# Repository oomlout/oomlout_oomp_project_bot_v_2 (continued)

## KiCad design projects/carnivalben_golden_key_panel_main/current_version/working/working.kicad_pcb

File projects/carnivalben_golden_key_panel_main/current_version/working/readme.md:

# golden_key
 
## summary 
* id: carnivalben_golden_key_panel_main
* user: carnivalben
* name: golden_key
* board: panel_main
* repo: https://github.com/CarnivalBen/golden-key
* src_file_repo_kicad_pcb: panel/pcb-main/panel-main - Copy.kicad_pcb
* src_file_repo_kicad_pcb_link: https://github.com/CarnivalBen/golden-key/tree/master/panel/pcb-main/panel-main - Copy.kicad_pcb

* src_file_repo_sch: layout-diag/layout-diag.sch
* src_file_repo_sch_link: https://github.com/CarnivalBen/golden-key/tree/master/layout-diag/layout-diag.sch
* full details link: https://github.com/oomlout/oomlout_oomp_project_bot_v_2/tree/main/projects/carnivalben_golden_key_panel_main/current_version/working  

## pcb  

[board (pdf)](working.pdf)  

## working_bom
| Id | Designator | Footprint | Quantity | Designation | Supplier and ref |  | None | 
| --- | --- | --- | --- | --- | --- | --- | --- | 
| 1 | C1,C2 | CP_Radial_D10.0mm_P5.00mm | 2 | 470uF |  |  | [''] | 
| 2 | C3 | C_Disc_D4.7mm_W2.5mm_P5.00mm | 1 | 10nF |  |  | [''] | 
| 3 | C4,C5 | C_Disc_D3.4mm_W2.1mm_P2.50mm | 2 | 33pF |  |  | [''] | 
| 4 | C6,C7 | CP_Radial_D18.0mm_P7.50mm | 2 | 4700uF |  |  | [''] | 
| 5 | D1,D2,D3,D4,D5,D6,D7,D8,D9,D10,D11,D12,D13,D14,D15,D16,D17,D18 | D_DO-15_P12.70mm_Horizontal | 18 | 1N4001 |  |  | [''] | 
| 6 | D19 | D_DO-15_P10.16mm_Horizontal | 1 | 12V |  |  | [''] | 
| 7 | D20 | D_DO-15_P10.16mm_Horizontal | 1 | 5V |  |  | [''] | 
| 8 | J1 | Wire_Pads_Edge_1x2 | 1 | PSU IN |  |  | [''] | 
| 9 | J2 | DIN_Socket_Edge_Solder_4pin | 1 | SPEED CTRL |  |  | [''] | 
| 10 | J3 | Pin_Header_Straight_1x06_Pitch2.54mm | 1 | ICSP |  |  | [''] | 
| 11 | J5 | Pin_Header_Straight_2x06_Pitch2.54mm | 1 | DISPLAY |  |  | [''] | 
| 12 | J6 | Wire_Pads_Edge_2x8 | 1 | CONN-L1 |  |  | [''] | 
| 13 | J7 | Wire_Pads_Edge_2x8 | 1 | CONN-L2 |  |  | [''] | 
| 14 | J8 | Wire_Pads_Edge_2x8 | 1 | CONN-R1 |  |  | [''] | 
| 15 | J9 | Wire_Pads_Edge_2x3 | 1 | CONN-R2 |  |  | [''] | 
| 16 | K1,K2,K3,K4,K5,K6,K7,K8,K9,K10,K11 | TRK22X3-XXDC | 11 | TRK2233-12DC |  |  | [''] | 
| 17 | Q1,Q14 | TO-92_Inline_Wide | 2 | 2N2222 |  |  | [''] | 
| 18 | Q2,Q9 | TO-220-3_Vertical | 2 | TIP32 |  |  | [''] | 
| 19 | Q3,Q4,Q5,Q6,Q7,Q8,Q10,Q11,Q12,Q13,Q15,Q16,Q17,Q18,Q19,Q37 | TO-126_Vertical | 16 | BD679 |  |  | [''] | 
| 20 | R1 | R_Axial_DIN0207_L6.3mm_D2.5mm_P10.16mm_Horizontal | 1 | 10K |  |  | [''] | 
| 21 | R2,R3,R8,R9 | R_Axial_DIN0207_L6.3mm_D2.5mm_P10.16mm_Horizontal | 4 | 5K |  |  | [''] | 
| 22 | R4,R5,R6,R7,R10,R11,R12,R13,R14,R15,R16,R17,R18,R19,R20,R21 | R_Axial_DIN0207_L6.3mm_D2.5mm_P10.16mm_Horizontal | 16 | 1K |  |  | [''] | 
| 23 | U1 | TO-220-3_Vertical | 1 | LM7805_TO220 |  |  | [''] | 
| 24 | U2,U3,U4,U5 | DIP-16_W7.62mm_LongPads | 4 | 74HC595 |  |  | [''] | 
| 25 | U6,U7 | DIP-16_W7.62mm_LongPads | 2 | ULN2003A |  |  | [''] | 
| 26 | U***1 | DIP-40_W15.24mm_LongPads | 1 | PIC16F877A |  |  | [''] | 
| 27 | Y1 | Crystal_HC49-U_Vertical | 1 | 20MHz |  |  | [''] | 
| 28 | J4 | Pin_Header_Straight_2x06_Pitch2.54mm | 1 | PUSH-BUTTON |  |  | [''] |

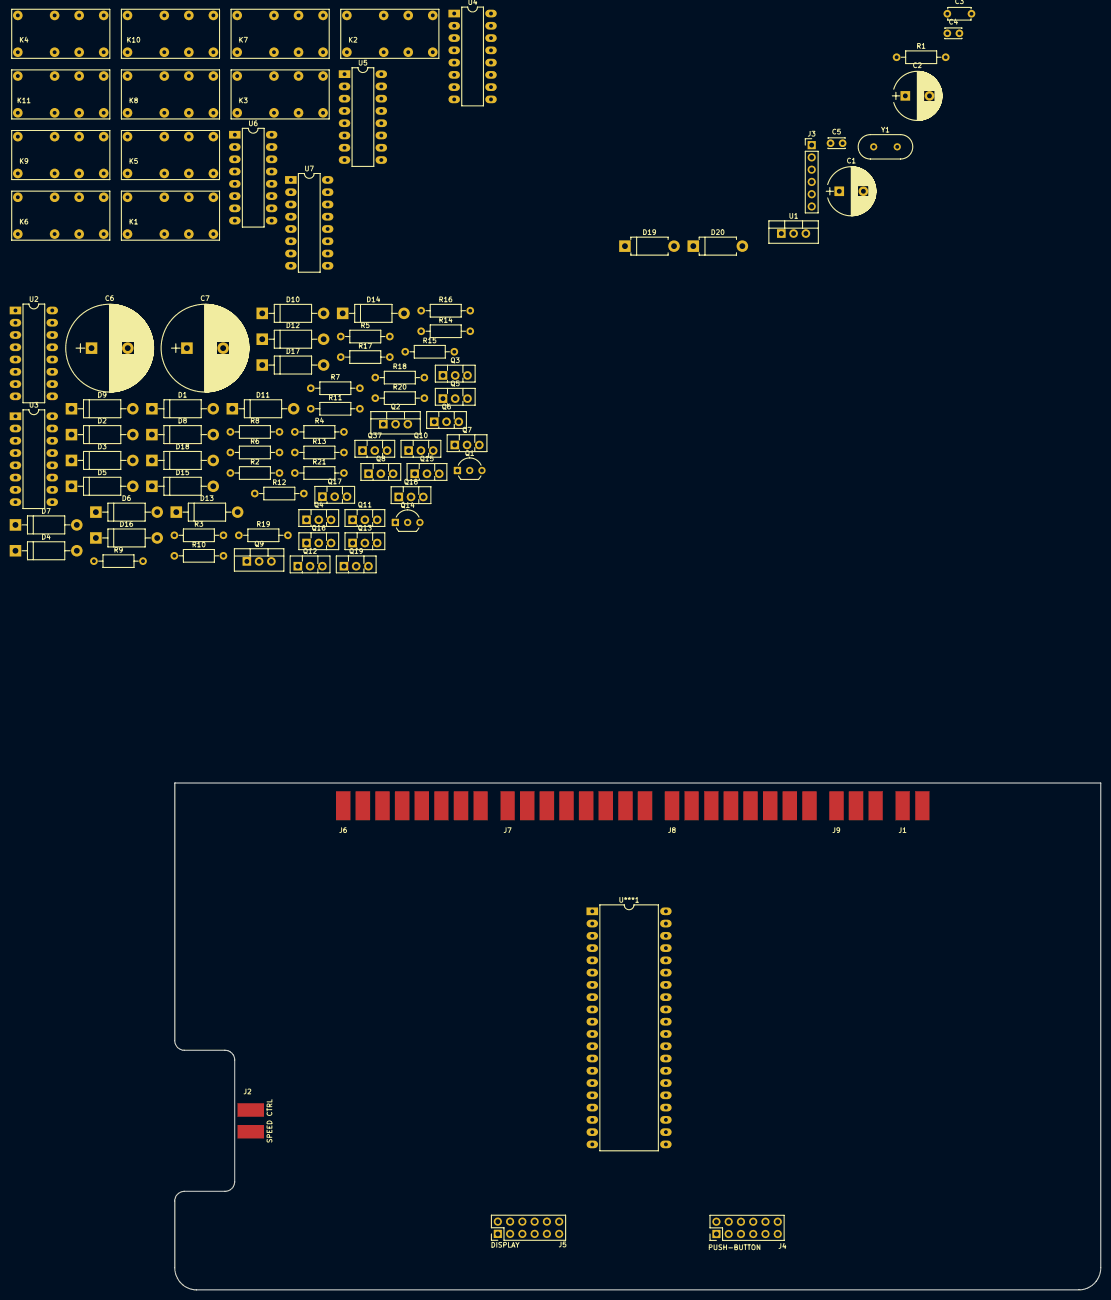
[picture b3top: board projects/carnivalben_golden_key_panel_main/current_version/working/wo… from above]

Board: 2 copper layers, 191.7 x 104.9 mm, 97 parts (0 on the bottom side), 131 nets, no tracks yet.

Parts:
C1, C2: 470uF; CP_Radial_D10.0mm_P5.00mm
C3: 10nF; C_Disc_D4.7mm_W2.5mm_P5.00mm
C4, C5: 33pF; C_Disc_D3.4mm_W2.1mm_P2.50mm
C6, C7: 4700uF; CP_Radial_D18.0mm_P7.50mm
D1, D2, D3, D4, D5, D6, D7, D8, D9, D10, D11, D12, D13, D14, D15, D16, D17, D18: 1N4001; D_DO-15_P12.70mm_Horizontal
D19: 12V; D_DO-15_P10.16mm_Horizontal
D20: 5V; D_DO-15_P10.16mm_Horizontal
J1: PSU IN; Wire_Pads_Edge_1x2
J2: SPEED CTRL; DIN_Socket_Edge_Solder_4pin
J3: ICSP; Pin_Header_Straight_1x06_Pitch2.54mm
J4: PUSH-BUTTON; Pin_Header_Straight_2x06_Pitch2.54mm
J5: DISPLAY; Pin_Header_Straight_2x06_Pitch2.54mm
J6: CONN-L1; Wire_Pads_Edge_2x8
J7: CONN-L2; Wire_Pads_Edge_2x8
J8: CONN-R1; Wire_Pads_Edge_2x8
J9: CONN-R2; Wire_Pads_Edge_2x3
K1, K2, K3, K4, K5, K6, K7, K8, K9, K10, K11: TRK2233-12DC; TRK22X3-XXDC
Q1, Q14: 2N2222; TO-92_Inline_Wide
Q2, Q9: TIP32; TO-220-3_Vertical
Q3, Q4, Q5, Q6, Q7, Q8, Q10, Q11, Q12, Q13, Q15, Q16, Q17, Q18, Q19, Q37: BD679; TO-126_Vertical
R1: 10K; R_Axial_DIN0207_L6.3mm_D2.5mm_P10.16mm_Horizontal
R2, R3, R8, R9: 5K; R_Axial_DIN0207_L6.3mm_D2.5mm_P10.16mm_Horizontal
R4, R5, R6, R7, R10, R11, R12, R13, R14, R15, R16, R17, R18, R19, R20, R21: 1K; R_Axial_DIN0207_L6.3mm_D2.5mm_P10.16mm_Horizontal
U1: LM7805_TO220; TO-220-3_Vertical
U2, U3, U4, U5: 74HC595; DIP-16_W7.62mm_LongPads
U6, U7: ULN2003A; DIP-16_W7.62mm_LongPads
U***1: PIC16F877A; DIP-40_W15.24mm_LongPads
Y1: 20MHz; Crystal_HC49-U_Vertical

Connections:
+5V: C2.1, C3.1, D20.1, J3.2, J5.4, J5.12, J7.13, R1.2, U1.3, U2.10, U2.16, U3.10, U3.16, U4.10, U4.16, U5.10, U5.16, U***1.11, U***1.32
+12V: C1.1, D1.2, D4.2, D19.1, J1.2, J2.4, J5.1, K1.1, K2.1, K3.1, K4.1, K5.1, K6.1, K6.3, K6.6, K7.1, K8.1, K9.1, K9.3, K9.6, K10.1, K11.1, U1.1, U6.9, U7.9
/AUX1-LED: J5.11, U***1.25
/AUX2-LED: J5.10, U***1.26
/Feed Relays/AUX[1]: J7.5, J9.1, K6.4, K6.5
/Feed Relays/AUX[2]: J7.6, J9.2, K9.4, K9.5
/Feed Relays/DATA[IN]: U4.14, U***1.15
/Feed Relays/FEED[A+]: J6.1, J8.1, K1.4
/Feed Relays/FEED[A-]: J6.2, K1.5
/Feed Relays/FEED[B+]: J8.2, K3.4
/Feed Relays/FEED[B-]: J8.3, K3.5
/Feed Relays/FEED[C+]: J6.3, J8.4, K5.4
/Feed Relays/FEED[C-]: J6.4, J8.5, K5.5
/Feed Relays/FEED[D+]: J6.5, K7.4
/Feed Relays/FEED[D-]: J6.6, J8.6, K7.5
/Feed Relays/FEED[E+]: J7.1, K8.4, K8.5
/Feed Relays/FEED[F+]: J7.2, K10.4, K10.5
/Feed Relays/FEED[G+]: J7.3, K11.4, K11.5
/Feed Relays/FEED[H+]: J7.4, K2.4, K2.5
/Feed Relays/FEED[I-]: J8.7, K4.4, K4.5
/HALL[E]: J7.12, U***1.4
/HALL[F]: J7.11, U***1.3
/HALL[G]: J7.10, U***1.2
/PB1: J4.1, U***1.30
/PB2: J4.2, U***1.29
/PB3: J4.3, U***1.28
/PB4: J4.4, U***1.27
/PB5: J4.5, U***1.22
/PB6: J4.12, U***1.21
/PB7: J4.11, U***1.20
/PB8: J4.10, U***1.19
/PB9: J4.9, U***1.8
/PB10: J4.8, U***1.9
/Points Control/DATA[IN]: U2.14, U5.9
/Points Control/DATA[OUT]: J5.2, U3.9
/Points Control/PB1: R4.1, U2.15
/Points Control/PB2: R6.1, U2.1
/Points Control/PB3: R10.1, U2.2
/Points Control/PB4: R12.1, U2.3
/Points Control/PB5: R14.1, U2.4
/Points Control/PB6: R16.1, U2.5
/Points Control/PB7: R18.1, U2.6
/Points Control/PB8: R20.1, U2.7
/Points Control/PF1: R5.1, U3.15
/Points Control/PF2: R7.1, U3.1
/Points Control/PF3: R11.1, U3.2
/Points Control/PF4: R13.1, U3.3
/Points Control/PF5: R15.1, U3.4
/Points Control/PF6: R17.1, U3.5
/Points Control/PF7: R19.1, U3.6
/Points Control/PF8: R21.1, U3.7
/Points Control/POINTS[B1]-COIL: D2.1, J8.16, Q37.3
/Points Control/POINTS[B2]-COIL: D5.1, J8.14, Q4.3
/Points Control/POINTS[B3]-COIL: D7.1, J8.12, Q6.3
/Points Control/POINTS[B4]-COIL: D9.1, J8.10, Q8.3
/Points Control/POINTS[B5]-COIL: D11.1, J6.16, Q11.3
/Points Control/POINTS[B6]-COIL: D13.1, J6.14, Q13.3
/Points Control/POINTS[B7]-COIL: D15.1, J6.12, Q16.3
/Points Control/POINTS[B8]-COIL: D17.1, J6.10, Q18.3
/Points Control/POINTS[F1]-COIL: D3.1, J8.15, Q3.3
/Points Control/POINTS[F2]-COIL: D6.1, J8.13, Q5.3
/Points Control/POINTS[F3]-COIL: D8.1, J8.11, Q7.3
/Points Control/POINTS[F4]-COIL: D10.1, J8.9, Q10.3
/Points Control/POINTS[F5]-COIL: D12.1, J6.15, Q12.3
/Points Control/POINTS[F6]-COIL: D14.1, J6.13, Q15.3
/Points Control/POINTS[F7]-COIL: D16.1, J6.11, Q17.3
/Points Control/POINTS[F8]-COIL: D18.1, J6.9, Q19.3
/Points Control/TANK[1]: R2.2, U***1.33
/Points Control/TANK[2]: R9.2, U***1.34
DCLK: J5.3, U2.11, U3.11, U4.11, U5.11, U***1.16
DLAT: J5.5, U2.12, U3.12, U4.12, U5.12, U***1.17
GND: C1.2, C2.2, C3.2, C4.2, C5.2, C6.2, C7.2, D2.2, D3.2, D5.2, D6.2, D7.2, D8.2, D9.2, D10.2, D11.2, D12.2, D13.2, D14.2, D15.2, D16.2, D17.2, D18.2, D19.2, D20.2, J1.1, J2.1, J3.3, J5.8, J6.7, J6.8, J7.7, J7.8, J7.9, J9.4, J9.5, J9.6, Q1.3, Q14.3, U1.2, U2.8, U2.13, U3.8, U3.13, U4.8, U4.13, U5.8, U5.13, U6.8, U7.8, U***1.12, U***1.31
ICSPCLK: J3.5, U***1.39
ICSPDAT: J3.4, U***1.40
MCLR: J3.1, R1.1, U***1.1
unnamed: C4.1, U***1.13, Y1.1
unnamed: C5.1, U***1.14, Y1.2
unnamed: C6.1, D1.1, Q2.3
unnamed: C7.1, D4.1, Q9.3
unnamed: K1.8, U6.16
unnamed: K2.8, U7.16
unnamed: K3.8, U6.15
unnamed: K4.8, U7.15
unnamed: K5.8, U6.14
unnamed: K6.8, U7.13
unnamed: K7.8, U6.13
unnamed: K8.8, U6.12
unnamed: K9.8, U7.12
unnamed: K10.8, U6.11
unnamed: K11.8, U6.10
unnamed: Q1.1, R3.1
unnamed: Q1.2, R2.1
unnamed: Q2.1, R3.2
unnamed: Q3.1, R5.2
unnamed: Q4.1, R6.2
unnamed: Q5.1, R7.2
unnamed: Q6.1, R10.2
unnamed: Q7.1, R11.2
unnamed: Q8.1, R12.2
unnamed: Q9.1, R8.2
unnamed: Q10.1, R13.2
unnamed: Q11.1, R14.2
unnamed: Q12.1, R15.2
unnamed: Q13.1, R16.2
unnamed: Q14.1, R8.1
unnamed: Q14.2, R9.1
unnamed: Q15.1, R17.2
unnamed: Q16.1, R18.2
unnamed: Q17.1, R19.2
unnamed: Q18.1, R20.2
unnamed: Q19.1, R21.2
unnamed: Q37.1, R4.2
unnamed: U2.9, U3.14
unnamed: U4.1, U6.2
unnamed: U4.2, U6.3
unnamed: U4.3, U6.4
unnamed: U4.4, U6.5
unnamed: U4.5, U6.6
unnamed: U4.6, U6.7
unnamed: U4.7, U7.1
unnamed: U4.9, U5.14
unnamed: U4.15, U6.1
unnamed: U5.1, U7.3
unnamed: U5.2, U7.4
unnamed: U5.3, U7.5
unnamed: U5.4, U7.6
unnamed: U5.5, U7.7
unnamed: U5.15, U7.2
TANK-DUMP: Q2.2, Q3.2, Q4.2, Q5.2, Q6.2, Q7.2, Q8.2, Q9.2, Q10.2, Q11.2, Q12.2, Q13.2, Q15.2, Q16.2, Q17.2, Q18.2, Q19.2, Q37.2
TRACK+: J2.3, K1.3, K2.3, K2.6, K3.3, K5.3, K7.3, K8.3, K8.6, K10.3, K10.6, K11.3, K11.6
TRACK-: J2.2, K1.6, K3.6, K4.3, K4.6, K5.6, K7.6

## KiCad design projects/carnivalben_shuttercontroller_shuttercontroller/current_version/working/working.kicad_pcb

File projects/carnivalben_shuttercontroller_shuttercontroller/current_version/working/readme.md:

# shuttercontroller
 
## summary 
* id: carnivalben_shuttercontroller_shuttercontroller
* user: carnivalben
* name: shuttercontroller
* board: shuttercontroller
* repo: https://github.com/CarnivalBen/ShutterController
* src_file_repo_kicad_pcb: PCB/ShutterController.kicad_pcb
* src_file_repo_kicad_pcb_link: https://github.com/CarnivalBen/ShutterController/tree/master/PCB/ShutterController.kicad_pcb

* src_file_repo_sch: PCB/ShutterController.sch
* src_file_repo_sch_link: https://github.com/CarnivalBen/ShutterController/tree/master/PCB/ShutterController.sch
* full details link: https://github.com/oomlout/oomlout_oomp_project_bot_v_2/tree/main/projects/carnivalben_shuttercontroller_shuttercontroller/current_version/working  

## schematic  
  
[schematic (pdf)](working_schematic.pdf) 

## pcb  

[board (pdf)](working.pdf)  

## working_bom
| Id | Designator | Footprint | Quantity | Designation | Supplier and ref |  | None | 
| --- | --- | --- | --- | --- | --- | --- | --- | 
| 1 | C1,C2 | CP_Radial_D10.0mm_P5.00mm | 2 | 470uF |  |  | [''] | 
| 2 | C3 | C_Disc_D3.0mm_W1.6mm_P2.50mm | 1 | 10nF |  |  | [''] | 
| 3 | D1 | LED_D5.0mm | 1 | OPEN |  |  | [''] | 
| 4 | D2 | LED_D5.0mm | 1 | HOLD |  |  | [''] | 
| 5 | D3 | LED_D5.0mm | 1 | CLOSE |  |  | [''] | 
| 6 | D4 | LED_D5.0mm | 1 | LOWER |  |  | [''] | 
| 7 | D5 | LED_D5.0mm | 1 | RAISE |  |  | [''] | 
| 8 | J1 | TerminalBlock_Phoenix_MKDS1.5-3pol | 1 | Screw_Terminal_01x03 |  |  | [''] | 
| 9 | J2 | TerminalBlock_Phoenix_MKDS1.5-2pol | 1 | Screw_Terminal_01x02 |  |  | [''] | 
| 10 | Q1,Q2,Q3,Q8,Q9 | TO-92_Inline_Wide | 5 | BC547 |  |  | [''] | 
| 11 | Q4 | TO-220-3_Vertical | 1 | BD437 |  |  | [''] | 
| 12 | Q5,Q6,Q7 | TO-92_Inline_Wide | 3 | TS13003 |  |  | [''] | 
| 13 | R1,R2,R3,R9,R10 | R_Axial_DIN0207_L6.3mm_D2.5mm_P10.16mm_Horizontal | 5 | 100K |  |  | [''] | 
| 14 | R4,R5,R6,R7,R8 | R_Axial_DIN0207_L6.3mm_D2.5mm_P10.16mm_Horizontal | 5 | 47 |  |  | [''] | 
| 15 | R11 | R_Axial_DIN0207_L6.3mm_D2.5mm_P10.16mm_Horizontal | 1 | 1.5K |  |  | [''] | 
| 16 | R12 | R_Axial_DIN0207_L6.3mm_D2.5mm_P10.16mm_Horizontal | 1 | 1K |  |  | [''] | 
| 17 | R13,R14,R15,R16,R17,R18 | R_Axial_DIN0207_L6.3mm_D2.5mm_P10.16mm_Horizontal | 6 | 100 |  |  | [''] | 
| 18 | RV1,RV3 | Potentiometer_Trimmer_Piher_PT-10v5_Horizontal_Px5.0mm_Py5.0mm | 2 | 1K |  |  | [''] | 
| 19 | RV2 | Potentiometer_Trimmer_Piher_PT-10v5_Horizontal_Px5.0mm_Py5.0mm | 1 | 5K |  |  | [''] | 
| 20 | U1 | TO-220-3_Vertical | 1 | LM7805 |  |  | [''] | 
| 21 | U2 | DIP-18_W7.62mm_LongPads | 1 | PIC16(L)F627A-I/P |  |  | [''] | 

## bom_schematic
| Ref | Qnty | Value | Cmp name | Footprint | Description | Vendor | DNP | 
| --- | --- | --- | --- | --- | --- | --- | --- | 
| C1, C2 | 2 | 470uF | CP | Capacitors_THT:CP_Radial_D10.0mm_P5.00mm |  |  |  | 
| C3 | 1 | 10nF | C | Capacitors_THT:C_Disc_D3.0mm_W1.6mm_P2.50mm |  |  |  | 
| D1, D2, D3, D4, D5 | 5 | LED | LED | LEDs:LED_D5.0mm |  |  |  | 
| J1 | 1 | Screw_Terminal_01x03 | Screw_Terminal_01x03 | TerminalBlocks_Phoenix:TerminalBlock_Phoenix_MKDS1.5-3pol |  |  |  | 
| J2 | 1 | Screw_Terminal_01x02 | Screw_Terminal_01x02 | TerminalBlocks_Phoenix:TerminalBlock_Phoenix_MKDS1.5-2pol |  |  |  | 
| Q1, Q2, Q3, Q8, Q9 | 5 | BC547 | 2N2219 | TO_SOT_Packages_THT:TO-92_Inline_Wide |  |  |  | 
| Q4 | 1 | BD437 | 2SC1815 | TO_SOT_Packages_THT:TO-220-3_Vertical |  |  |  | 
| Q5, Q6, Q7 | 3 | TS13003 | 2SC1815 | TO_SOT_Packages_THT:TO-92_Inline_Wide |  |  |  | 
| R1, R2, R3, R9, R10 | 5 | 100K | R | Resistors_THT:R_Axial_DIN0207_L6.3mm_D2.5mm_P10.16mm_Horizontal |  |  |  | 
| R4, R5, R6, R7, R8 | 5 | 47 | R | Resistors_THT:R_Axial_DIN0207_L6.3mm_D2.5mm_P10.16mm_Horizontal |  |  |  | 
| R11 | 1 | 1.5K | R | Resistors_THT:R_Axial_DIN0207_L6.3mm_D2.5mm_P10.16mm_Horizontal |  |  |  | 
| R12 | 1 | 1K | R | Resistors_THT:R_Axial_DIN0207_L6.3mm_D2.5mm_P10.16mm_Horizontal |  |  |  | 
| R13, R14, R15, R16, R17, R18 | 6 | 100 | R | Resistors_THT:R_Axial_DIN0207_L6.3mm_D2.5mm_P10.16mm_Horizontal |  |  |  | 
| RV1, RV3 | 2 | 1K | POT_TRIM | Potentiometers:Potentiometer_Trimmer_Piher_PT-10v5_Horizontal_Px5.0mm_Py5.0mm |  |  |  | 
| RV2 | 1 | 5K | POT_TRIM | Potentiometers:Potentiometer_Trimmer_Piher_PT-10v5_Horizontal_Px5.0mm_Py5.0mm |  |  |  | 
| U1 | 1 | LM7805_TO220 | LM7805_TO220 | TO_SOT_Packages_THT:TO-220-3_Vertical |  |  |  | 
| U2 | 1 | PIC16(L)F627A-I/P | PIC16(L)F627A-I/P | Housings_DIP:DIP-18_W7.62mm_LongPads |  |  |  |

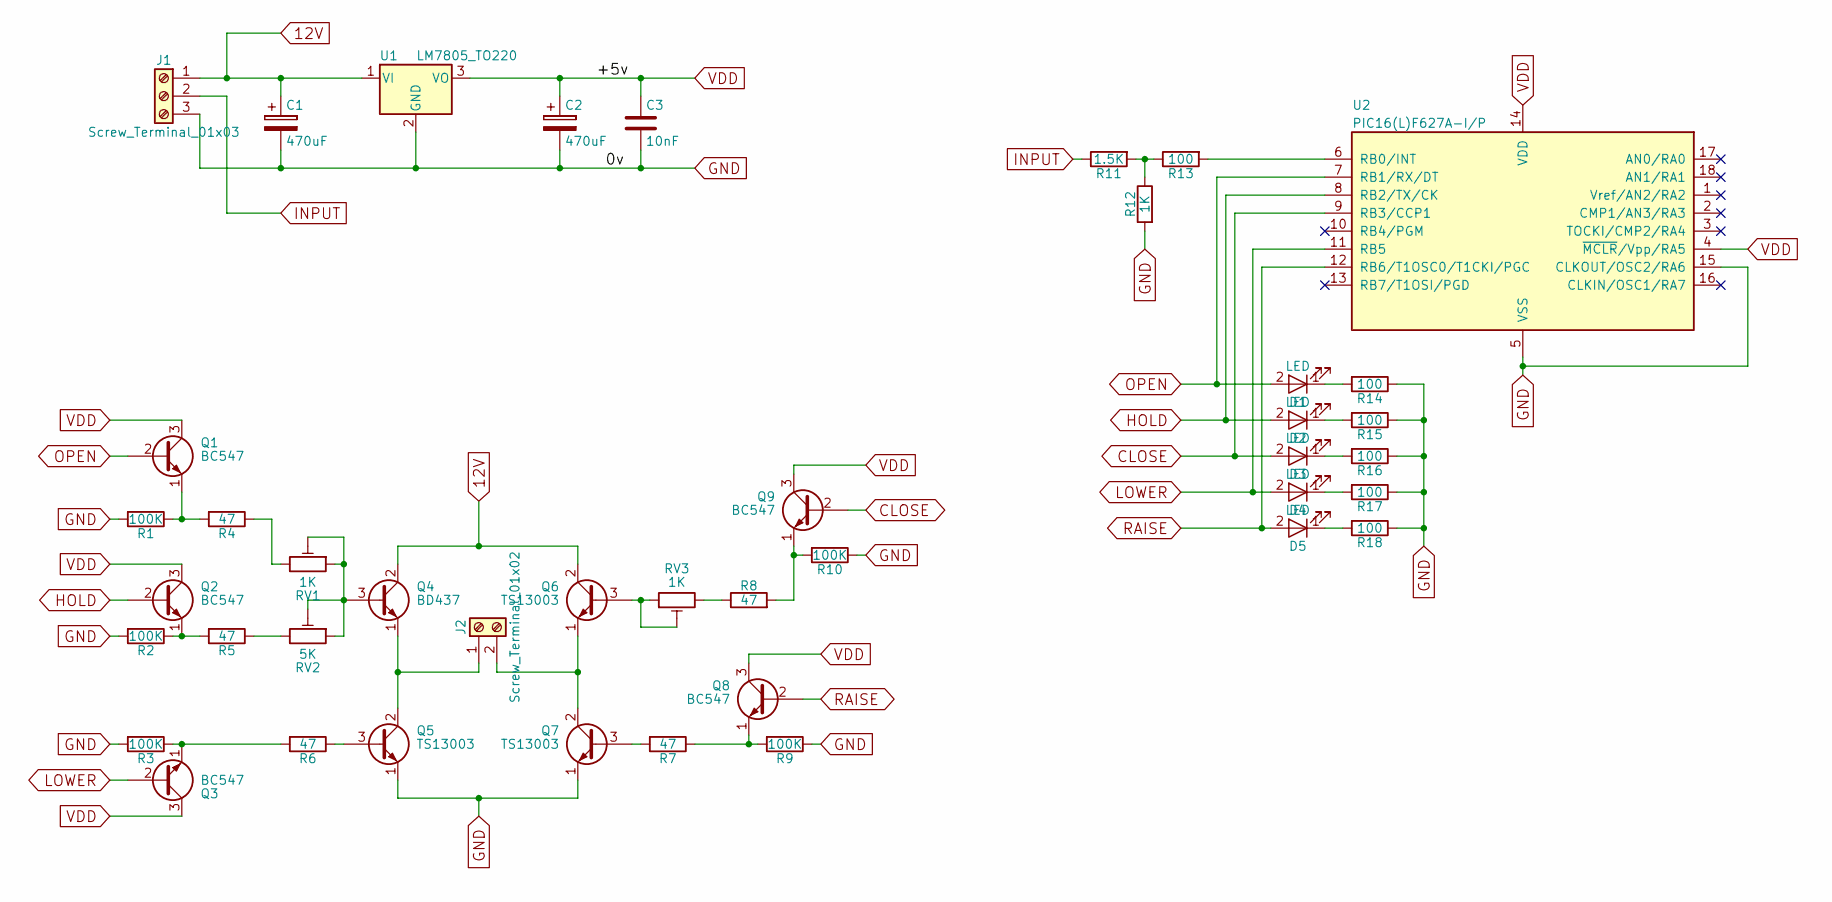
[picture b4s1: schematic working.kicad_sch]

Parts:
C1, C2: 470uF; CP_Radial_D10.0mm_P5.00mm
C3: 10nF; C_Disc_D3.0mm_W1.6mm_P2.50mm
D1, D2, D3, D4, D5: LED; LED_D5.0mm
J1: Screw_Terminal_01x03; TerminalBlock_Phoenix_MKDS1.5-3pol
J2: Screw_Terminal_01x02; TerminalBlock_Phoenix_MKDS1.5-2pol
Q1, Q2, Q3, Q8, Q9: BC547; TO-92_Inline_Wide
Q4: BD437; TO-220-3_Vertical
Q5, Q6, Q7: TS13003; TO-92_Inline_Wide
R1, R2, R3, R9, R10: 100K; R_Axial_DIN0207_L6.3mm_D2.5mm_P10.16mm_Horizontal
R4, R5, R6, R7, R8: 47; R_Axial_DIN0207_L6.3mm_D2.5mm_P10.16mm_Horizontal
R11: 1.5K; R_Axial_DIN0207_L6.3mm_D2.5mm_P10.16mm_Horizontal
R12: 1K; R_Axial_DIN0207_L6.3mm_D2.5mm_P10.16mm_Horizontal
R13, R14, R15, R16, R17, R18: 100; R_Axial_DIN0207_L6.3mm_D2.5mm_P10.16mm_Horizontal
RV1, RV3: 1K; Potentiometer_Trimmer_Piher_PT-10v5_Horizontal_Px5.0mm_Py5.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
RV2: 5K; Potentiometer_Trimmer_Piher_PT-10v5_Horizontal_Px5.0mm_Py5.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
U1: LM7805_TO220; TO-220-3_Vertical
U2: PIC16(L)F627A-I/P; DIP-18_W7.62mm_LongPads

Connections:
12V: C1.1, J1.1, Q4.2 (C), Q6.2 (C), U1.1 (VI)
CLOSE: D3.2 (A), Q9.2 (B), U2.9 (RB3/CCP1)
GND: C1.2, C2.2, C3.2, J1.3, Q5.1 (E), Q7.1 (E), R1.2, R2.2, R3.2, R9.1, R10.1, R12.2, R14.1, R15.1, R16.1, R17.1, R18.1, U1.2 (GND), U2.5 (VSS), U2.15 (CLKOUT/OSC2/RA6)
HOLD: D2.2 (A), Q2.2 (B), U2.8 (RB2/TX/CK)
INPUT: J1.2, R11.1
LOWER: D4.2 (A), Q3.2 (B), U2.11 (RB5)
unnamed: D1.1 (K), R14.2
unnamed: D2.1 (K), R15.2
unnamed: D3.1 (K), R16.2
unnamed: D4.1 (K), R17.2
unnamed: D5.1 (K), R18.2
unnamed: J2.1, Q4.1 (E), Q5.2 (C)
unnamed: J2.2, Q6.1 (E), Q7.2 (C)
unnamed: Q1.1 (E), R1.1, R4.2
unnamed: Q2.1 (E), R2.1, R5.2
unnamed: Q3.1 (E), R3.1, R6.2
unnamed: Q4.3 (B), RV1.1, RV1.2, RV2.1, RV2.2
unnamed: Q5.3 (B), R6.1
unnamed: Q6.3 (B), RV3.1, RV3.2
unnamed: Q7.3 (B), R7.2
unnamed: Q8.1 (E), R7.1, R9.2
unnamed: Q9.1 (E), R8.2, R10.2
unnamed: R4.1, RV1.3
unnamed: R5.1, RV2.3
unnamed: R8.1, RV3.3
unnamed: R11.2, R12.1, R13.1
unnamed: R13.2, U2.6 (RB0/INT)
OPEN: D1.2 (A), Q1.2 (B), U2.7 (RB1/RX/DT)
RAISE: D5.2 (A), Q8.2 (B), U2.12 (RB6/T1OSC0/T1CKI/PGC)
VDD: C2.1, C3.1, Q1.3 (C), Q2.3 (C), Q3.3 (C), Q8.3 (C), Q9.3 (C), U1.3 (VO), U2.4 (~MCLR/Vpp/RA5), U2.14 (VDD)

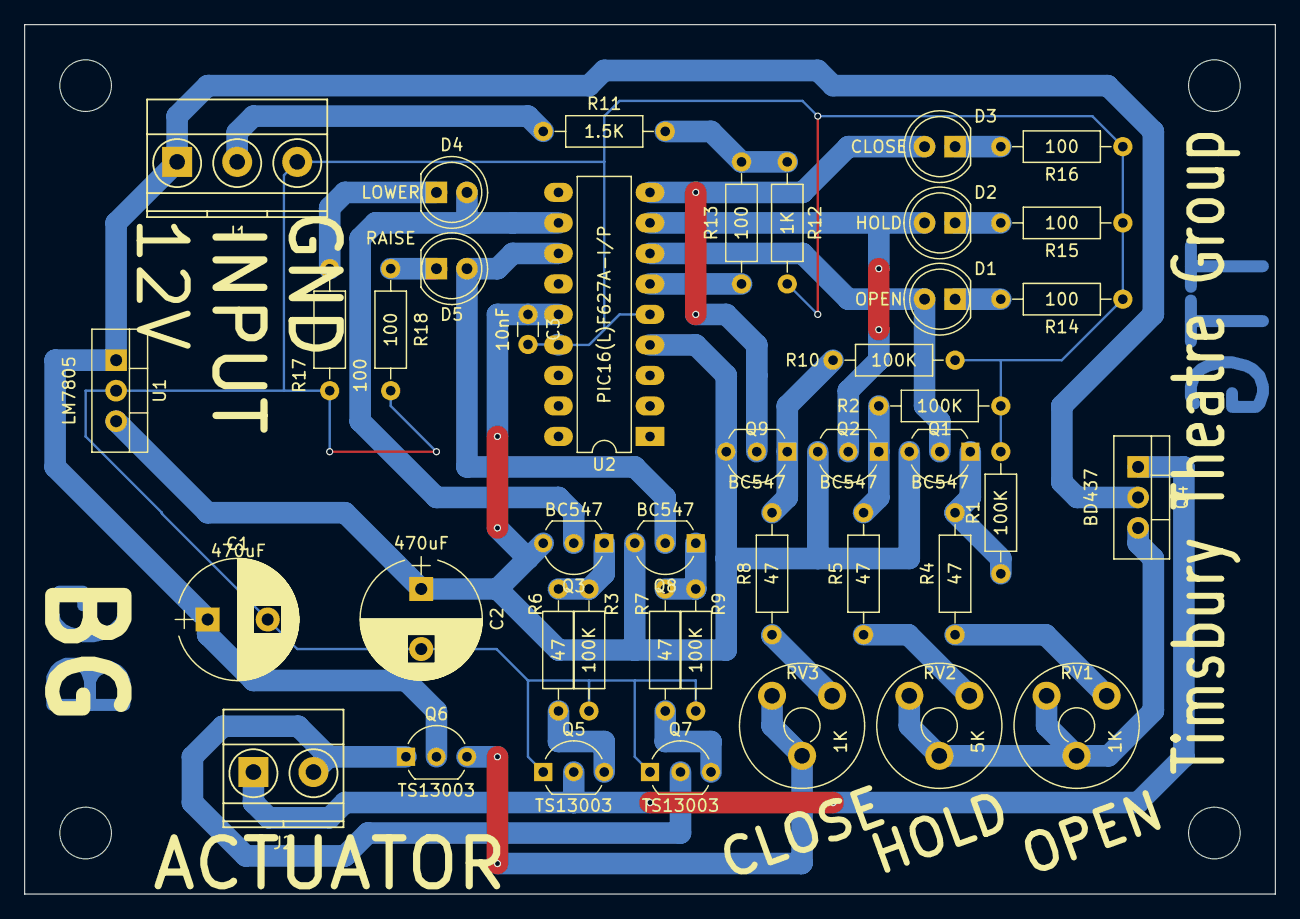
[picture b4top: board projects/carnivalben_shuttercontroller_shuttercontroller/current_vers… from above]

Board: 2 copper layers, 104.1 x 72.4 mm, 42 parts (0 on the bottom side), 30 nets.

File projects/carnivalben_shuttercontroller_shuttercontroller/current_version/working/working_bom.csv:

"Id";"Designator";"Footprint";"Quantity";"Designation";"Supplier and ref";
1;"C1,C2";"CP_Radial_D10.0mm_P5.00mm";2;"470uF";;;
2;"C3";"C_Disc_D3.0mm_W1.6mm_P2.50mm";1;"10nF";;;
3;"D1";"LED_D5.0mm";1;"OPEN";;;
4;"D2";"LED_D5.0mm";1;"HOLD";;;
5;"D3";"LED_D5.0mm";1;"CLOSE";;;
6;"D4";"LED_D5.0mm";1;"LOWER";;;
7;"D5";"LED_D5.0mm";1;"RAISE";;;
8;"J1";"TerminalBlock_Phoenix_MKDS1.5-3pol";1;"Screw_Terminal_01x03";;;
9;"J2";"TerminalBlock_Phoenix_MKDS1.5-2pol";1;"Screw_Terminal_01x02";;;
10;"Q1,Q2,Q3,Q8,Q9";"TO-92_Inline_Wide";5;"BC547";;;
11;"Q4";"TO-220-3_Vertical";1;"BD437";;;
12;"Q5,Q6,Q7";"TO-92_Inline_Wide";3;"TS13003";;;
13;"R1,R2,R3,R9,R10";"R_Axial_DIN0207_L6.3mm_D2.5mm_P10.16mm_Horizontal";5;"100K";;;
14;"R4,R5,R6,R7,R8";"R_Axial_DIN0207_L6.3mm_D2.5mm_P10.16mm_Horizontal";5;"47";;;
15;"R11";"R_Axial_DIN0207_L6.3mm_D2.5mm_P10.16mm_Horizontal";1;"1.5K";;;
16;"R12";"R_Axial_DIN0207_L6.3mm_D2.5mm_P10.16mm_Horizontal";1;"1K";;;
17;"R13,R14,R15,R16,R17,R18";"R_Axial_DIN0207_L6.3mm_D2.5mm_P10.16mm_Horizontal";6;"100";;;
18;"RV1,RV3";"Potentiometer_Trimmer_Piher_PT-10v5_Horizontal_Px5.0mm_Py5.0mm";2;"1K";;;
19;"RV2";"Potentiometer_Trimmer_Piher_PT-10v5_Horizontal_Px5.0mm_Py5.0mm";1;"5K";;;
20;"U1";"TO-220-3_Vertical";1;"LM7805";;;
21;"U2";"DIP-18_W7.62mm_LongPads";1;"PIC16(L)F627A-I/P";;;

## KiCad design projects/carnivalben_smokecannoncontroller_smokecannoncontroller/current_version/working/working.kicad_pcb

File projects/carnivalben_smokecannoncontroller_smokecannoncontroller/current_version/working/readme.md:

# smokecannoncontroller
 
## summary 
* id: carnivalben_smokecannoncontroller_smokecannoncontroller
* user: carnivalben
* name: smokecannoncontroller
* board: smokecannoncontroller
* repo: https://github.com/CarnivalBen/SmokeCannonController
* src_file_repo_kicad_pcb: SmokeCannonController.kicad_pcb
* src_file_repo_kicad_pcb_link: https://github.com/CarnivalBen/SmokeCannonController/tree/master/SmokeCannonController.kicad_pcb

* src_file_repo_sch: SmokeCannonController.sch
* src_file_repo_sch_link: https://github.com/CarnivalBen/SmokeCannonController/tree/master/SmokeCannonController.sch
* full details link: https://github.com/oomlout/oomlout_oomp_project_bot_v_2/tree/main/projects/carnivalben_smokecannoncontroller_smokecannoncontroller/current_version/working  

## schematic  
  
[schematic (pdf)](working_schematic.pdf) 

## pcb  

[board (pdf)](working.pdf)  

## working_bom
| Id | Designator | Footprint | Quantity | Designation | Supplier and ref |  | None | 
| --- | --- | --- | --- | --- | --- | --- | --- | 
| 1 | C2 | CP_Radial_D8.0mm_P3.80mm | 1 | 470uF |  |  | [''] | 
| 2 | D1 | TO-220-3_Vertical | 1 | BTA08-600C |  |  | [''] | 
| 3 | D2 | Diode_Bridge_Round_D9.8mm | 1 | D_Bridge_+-AA |  |  | [''] | 
| 4 | J1 | TerminalBlock_bornier-3_P5.08mm | 1 | SMOKE_MACHINE_XLR |  |  | [''] | 
| 5 | J2 | TerminalBlock_bornier-2_P5.08mm | 1 | LED_OUTPUT |  |  | [''] | 
| 6 | R1,R2 | R_Axial_DIN0207_L6.3mm_D2.5mm_P10.16mm_Horizontal | 2 | 100 |  |  | [''] | 
| 7 | R3 | R_Axial_Power_L20.0mm_W6.4mm_P25.40mm | 1 | 820 |  |  | [''] | 
| 8 | R4 | R_Axial_Power_L20.0mm_W6.4mm_P25.40mm | 1 | 30 |  |  | [''] | 
| 9 | RV1 | Potentiometer_Trimmer_Piher_PT-10v5_Horizontal_Px5.0mm_Py5.0mm | 1 | 100K |  |  | [''] | 
| 10 | RV2 | Potentiometer_Trimmer_Piher_PT-10v5_Horizontal_Px5.0mm_Py5.0mm | 1 | 1K |  |  | [''] | 
| 11 | U1 | DIP-6_W7.62mm | 1 | MOC3020M |  |  | [''] | 
| 12 | U3 | DIP-8_W7.62mm | 1 | LM555 |  |  | [''] | 
| 13 | C1 | C_Disc_D4.3mm_W1.9mm_P5.00mm | 1 | 0.01uF |  |  | [''] | 
| 14 | U2 | HLK-PM01 | 1 | PSU-5VDC |  |  | [''] | 

## bom_schematic
| Ref | Qnty | Value | Cmp name | Footprint | Description | Vendor | DNP | 
| --- | --- | --- | --- | --- | --- | --- | --- | 
| C1 | 1 | 0.01uF | C | Capacitors_THT:C_Disc_D4.3mm_W1.9mm_P5.00mm |  |  |  | 
| C2 | 1 | 470uF | CP | Capacitors_THT:CP_Radial_D8.0mm_P3.80mm |  |  |  | 
| D1 | 1 | BTA08-600C | Q_TRIAC_AAG2 | TO_SOT_Packages_THT:TO-220-3_Vertical |  |  |  | 
| D2 | 1 | D_Bridge_+-AA | D_Bridge_+A-A | Diodes_THT:Diode_Bridge_Round_D9.8mm |  |  |  | 
| J1 | 1 | SMOKE_MACHINE_XLR | Screw_Terminal_01x03 | Connectors_Terminal_Blocks:TerminalBlock_bornier-3_P5.08mm |  |  |  | 
| J2 | 1 | LED_OUTPUT | Screw_Terminal_01x02 | Connectors_Terminal_Blocks:TerminalBlock_bornier-2_P5.08mm |  |  |  | 
| R1, R2 | 2 | 100 | R | Resistors_THT:R_Axial_DIN0207_L6.3mm_D2.5mm_P10.16mm_Horizontal |  |  |  | 
| R3 | 1 | 820 | R | Resistors_THT:R_Axial_Power_L20.0mm_W6.4mm_P25.40mm |  |  |  | 
| R4 | 1 | 30 | R | Resistors_THT:R_Axial_Power_L20.0mm_W6.4mm_P25.40mm |  |  |  | 
| RV1 | 1 | 100K | POT_TRIM | Potentiometers:Potentiometer_Trimmer_Piher_PT-10v5_Horizontal_Px5.0mm_Py5.0mm |  |  |  | 
| RV2 | 1 | 1K | POT_TRIM | Potentiometers:Potentiometer_Trimmer_Piher_PT-10v5_Horizontal_Px5.0mm_Py5.0mm |  |  |  | 
| U1 | 1 | MOC3020M | MOC3020M | Housings_DIP:DIP-6_W7.62mm |  |  |  | 
| U2 | 1 | PSU-5VDC | PSU-5VDC | BGCustom:HLK-PM01 |  |  |  | 
| U3 | 1 | LM555 | LM555 | Housings_DIP:DIP-8_W7.62mm |  |  |  |

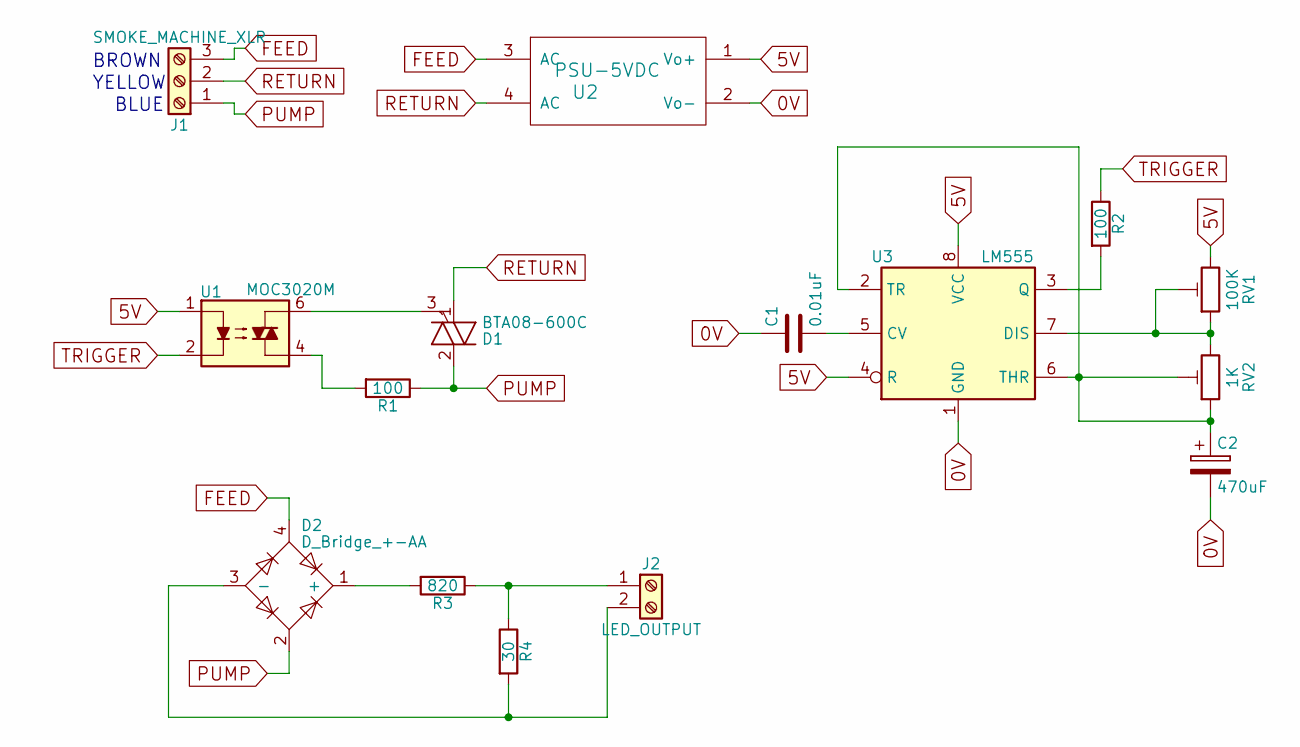
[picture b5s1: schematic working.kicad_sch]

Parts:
C1: 0.01uF; C_Disc_D4.3mm_W1.9mm_P5.00mm
C2: 470uF; CP_Radial_D8.0mm_P3.80mm
D1: BTA08-600C; TO-220-3_Vertical
D2: D_Bridge_+-AA; Diode_Bridge_Round_D9.8mm
J1: SMOKE_MACHINE_XLR; TerminalBlock_bornier-3_P5.08mm
J2: LED_OUTPUT; TerminalBlock_bornier-2_P5.08mm
R1, R2: 100; R_Axial_DIN0207_L6.3mm_D2.5mm_P10.16mm_Horizontal
R3: 820; R_Axial_Power_L20.0mm_W6.4mm_P25.40mm
R4: 30; R_Axial_Power_L20.0mm_W6.4mm_P25.40mm
RV1: 100K; Potentiometer_Trimmer_Piher_PT-10v5_Horizontal_Px5.0mm_Py5.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
RV2: 1K; Potentiometer_Trimmer_Piher_PT-10v5_Horizontal_Px5.0mm_Py5.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
U1: MOC3020M; DIP-6_W7.62mm
U2: PSU-5VDC; HLK-PM01
U3: LM555; DIP-8_W7.62mm

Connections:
0V: C1.1, C2.2, U2.2 (Vo-), U3.1 (GND)
5V: RV1.3, U1.1, U2.1 (Vo+), U3.4 (R), U3.8 (VCC)
FEED: D2.4, J1.3, U2.3 (AC)
unnamed: C1.2, U3.5 (CV)
unnamed: C2.1, RV2.1, RV2.2, U3.2 (TR), U3.6 (THR)
unnamed: D1.3 (G), U1.6
unnamed: D2.1 (+), R3.2
unnamed: D2.3 (-), J2.2, R4.2
unnamed: J2.1, R3.1, R4.1
unnamed: R1.2, U1.4
unnamed: R2.2, U3.3 (Q)
unnamed: RV1.1, RV1.2, RV2.3, U3.7 (DIS)
PUMP: D1.2 (A2), D2.2, J1.1, R1.1
RETURN: D1.1 (A1), J1.2, U2.4 (AC)
TRIGGER: R2.1, U1.2

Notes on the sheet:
YELLOW
BROWN
BLUE

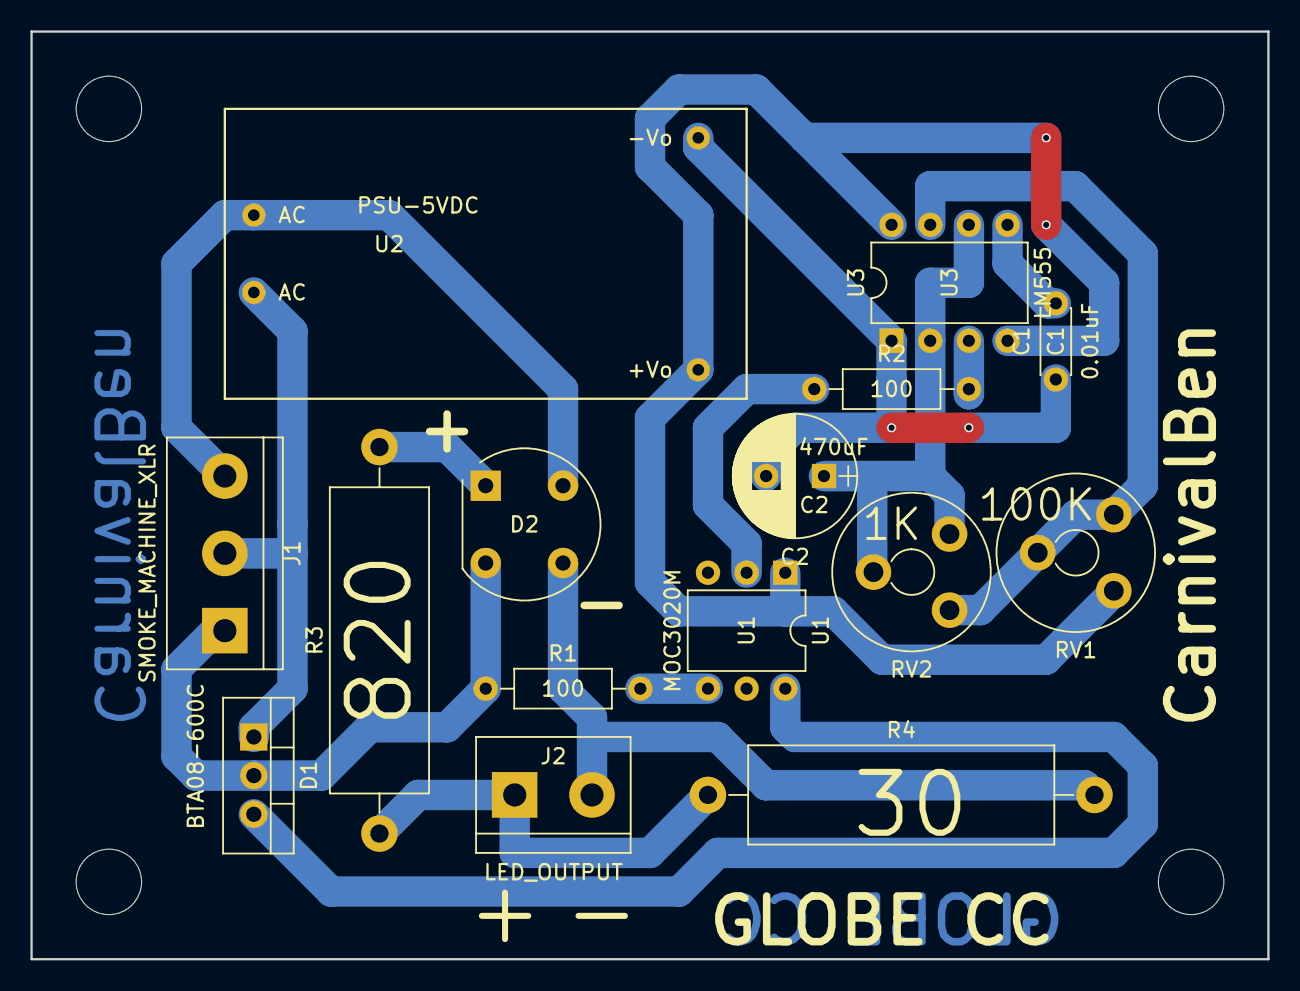
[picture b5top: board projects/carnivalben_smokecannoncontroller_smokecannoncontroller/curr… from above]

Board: 2 copper layers, 81.3 x 61.0 mm, 15 parts (0 on the bottom side), 15 nets.
